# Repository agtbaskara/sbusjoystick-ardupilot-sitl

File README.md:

# SBUS to USB Joystick Converter with Ardupilot SITL Support

## Requirement
- PC with Linux OS (Tested on Ubuntu 18.04)
- RC Transmitter (Tested on Frsky Taranis QX7)
- SBUS RC Receiver (Tested on Frsky X8R and FX400R)
- Arduino Pro Micro (or another ATmega32U4 based Arduino)
- SBUS Inverter (DIY Schematic and PCB design file in repository)

## Setup Instruction
- Install Arduino Joystick Library library (https://github.com/MHeironimus/ArduinoJoystickLibrary)
- Install this fork of FUTABA_SBUS library (https://github.com/agtbaskara/FUTABA_SBUS)
- Upload `sbusjoystick-ardupilot-sitl.ino` to Arduino
- (Optional) for Ardupilot SITL support copy `sbusjoystick.yml` to `~/.local/lib/python2.7/site-packages/MAVProxy/modules/mavproxy_joystick/joysticks`

## Button Mapping:
- Axis 0: Channel 0
- Axis 1: Channel 1
- Axis 2: Channel 10
- Axis 3: Channel 2
- Axis 4: Channel 3
- Axis 5: Channel 11
- Button 0: Channel 4 Low
- Button 1: Channel 4 Mid
- Button 2: Channel 4 High
- Button 3: Channel 5 Low
- Button 4: Channel 5 Mid
- Button 5: Channel 5 High
- Button 6: Channel 6 Low
- Button 7: Channel 6 Mid
- Button 8: Channel 6 High
- Button 9: Channel 7 Low
- Button 10: Channel 7 Mid
- Button 11: Channel 7 High
- Button 12: Channel 8 Low
- Button 13: Channel 8 High
- Button 14: Channel 9 Low
- Button 15: Channel 9 High

## To Do
- Add PPM RC Receiver Support

## Reference
- Source code based on https://github.com/Robinhuett/sbuscontroller, https://github.com/mikeshub/FUTABA_SBUS, and https://github.com/MHeironimus/ArduinoJoystickLibrary
- Hardware design based on https://oscarliang.com/diy-sbus-usb-converter/
- Configuration based on https://github.com/ArduPilot/MAVProxy/blob/master/docs/JOYSTICKS.md

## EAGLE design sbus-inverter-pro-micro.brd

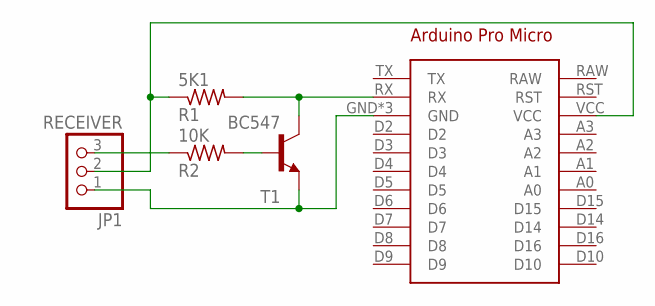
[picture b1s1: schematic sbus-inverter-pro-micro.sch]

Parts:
ARDUINO1: ARDUINO_PRO_MICRO
JP1: RECEIVER; 1X03/90
R1: 5K1; 0207/10
R2: 10K; 0207/10
T1: BC547; TO92

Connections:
unnamed: R2.2, T1.2 (B)
unnamed: ARDUINO1.GND, ARDUINO1.GND@1 (GND), ARDUINO1.GND@2 (GND), JP1.1, T1.1 (E)
unnamed: ARDUINO1.RX, R1.2, T1.3 (C)
unnamed: JP1.3, R2.1
unnamed: ARDUINO1.VCC, JP1.2, R1.1

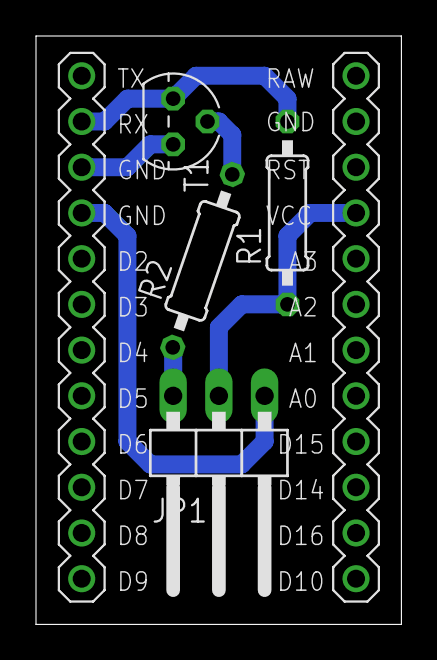
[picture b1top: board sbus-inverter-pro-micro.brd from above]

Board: 2 copper layers, 20.3 x 32.7 mm, 5 parts (0 on the bottom side), 5 nets.

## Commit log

2019-08-15 Add Code and Readme file
2019-12-18 Update From STM32F103C to Arduino Pro Micro
    Add SBUS Inverter Schematic and PCB design file
